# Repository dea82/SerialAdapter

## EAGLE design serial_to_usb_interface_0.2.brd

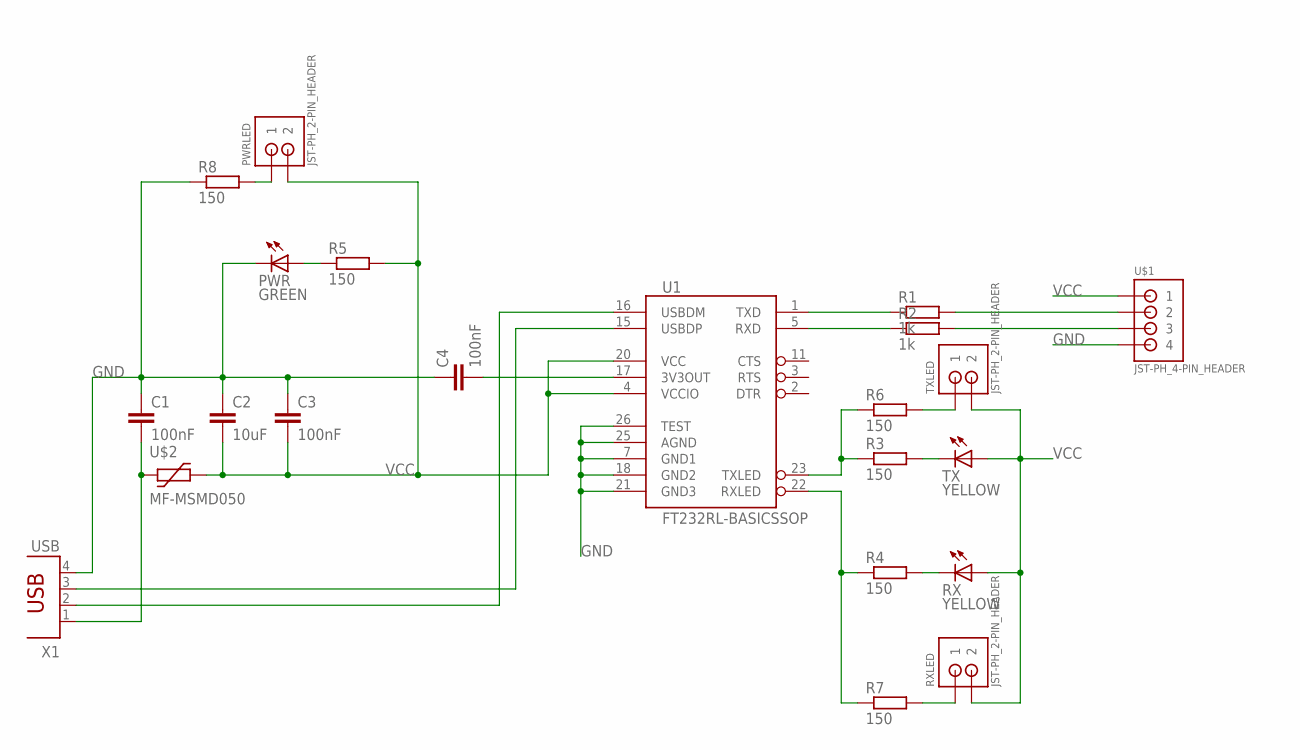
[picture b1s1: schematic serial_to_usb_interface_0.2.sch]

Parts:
C1, C3, C4: 100nF; C1206
C2: 10uF; C1206
PWR: GREEN; CHIPLED_0805
PWRLED: JST-PH_2-PIN_HEADER; JST_B2B-PH_HEADER
R1, R2: 1k; R1206
R3, R4, R5, R6, R7, R8: 150; R1206
RX: YELLOW; CHIPLED_0805
RXLED: JST-PH_2-PIN_HEADER; JST_B2B-PH_HEADER
TX: YELLOW; CHIPLED_0805
TXLED: JST-PH_2-PIN_HEADER; JST_B2B-PH_HEADER
U1: FT232RL-BASICSSOP; SSOP28DB
U$1: JST-PH_4-PIN_HEADER; JST_B4B-PH_HEADER
U$2: MF-MSMD050
X1: USB; PN87520

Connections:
GND: C1.1, C2.1, C3.1, C4.1, PWR.C, R8.1, U1.7 (GND1), U1.18 (GND2), U1.21 (GND3), U1.25 (AGND), U1.26 (TEST), U$1.P4 (4), X1.4
unnamed: R4.2, RX.C
unnamed: R3.1, R6.1, U1.23 (TXLED)
unnamed: C4.2, U1.17 (3V3OUT)
unnamed: U1.15 (USBDP), X1.3
unnamed: U1.16 (USBDM), X1.2
unnamed: C1.2, U$2.P$1 (1), X1.1
unnamed: R1.1, U1.1 (TXD)
unnamed: R2.1, U1.5 (RXD)
unnamed: R1.2, U$1.P2 (2)
unnamed: R2.2, U$1.P3 (3)
unnamed: R4.1, R7.1, U1.22 (RXLED)
unnamed: R3.2, TX.C
unnamed: R7.2, RXLED.P1 (1)
unnamed: PWR.A, R5.1
PWRLED: PWRLED.P1 (1), R8.2
TXLED: R6.2, TXLED.P1 (1)
VCC: C2.2, C3.2, PWRLED.P2 (2), R5.2, RX.A, RXLED.P2 (2), TX.A, TXLED.P2 (2), U1.4 (VCCIO), U1.20 (VCC), U$1.P1 (1), U$2.P$2 (2)

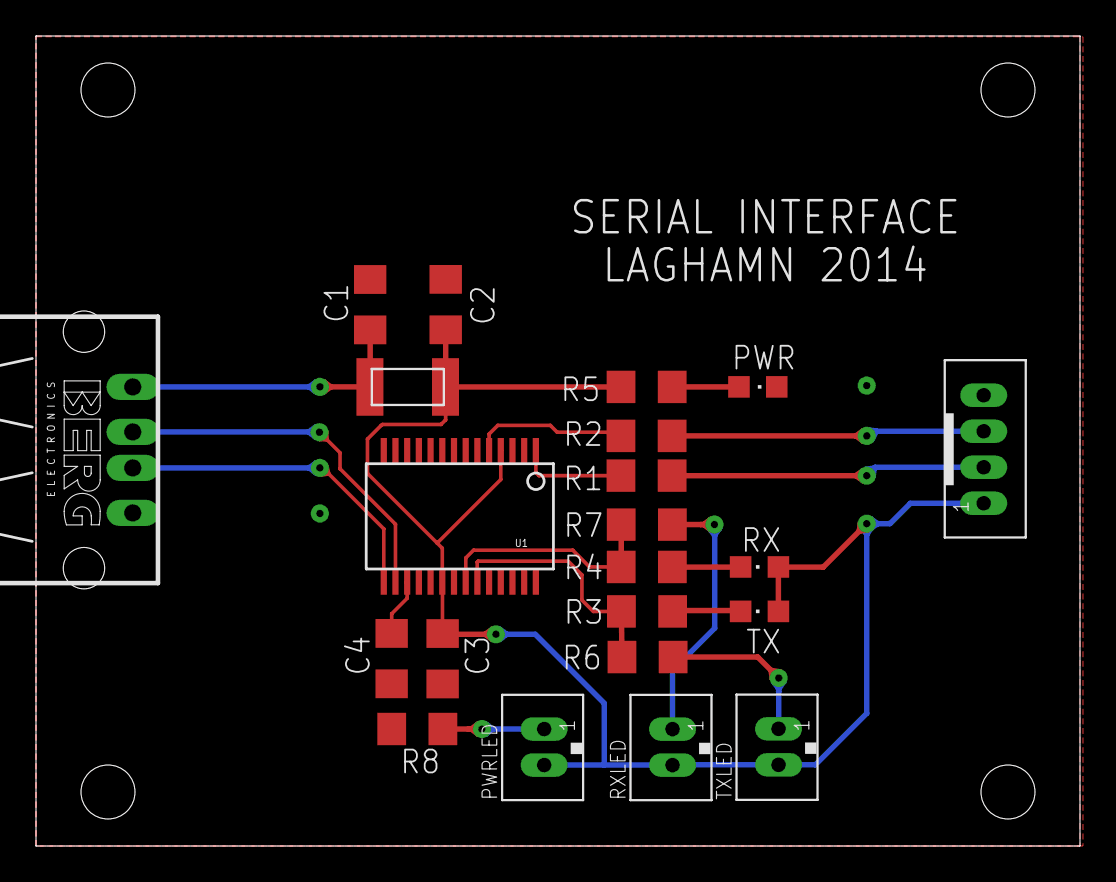
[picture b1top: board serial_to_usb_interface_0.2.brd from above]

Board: 2 copper layers, 58.0 x 45.0 mm, 22 parts (0 on the bottom side), 18 nets.

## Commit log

2015-09-11 Added eagle files.

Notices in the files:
parts and their libraries:
SparkFun-DigitalIC: Licensing: CC v3.0 Share-Alike You are welcome to use this library for commercial purposes.
